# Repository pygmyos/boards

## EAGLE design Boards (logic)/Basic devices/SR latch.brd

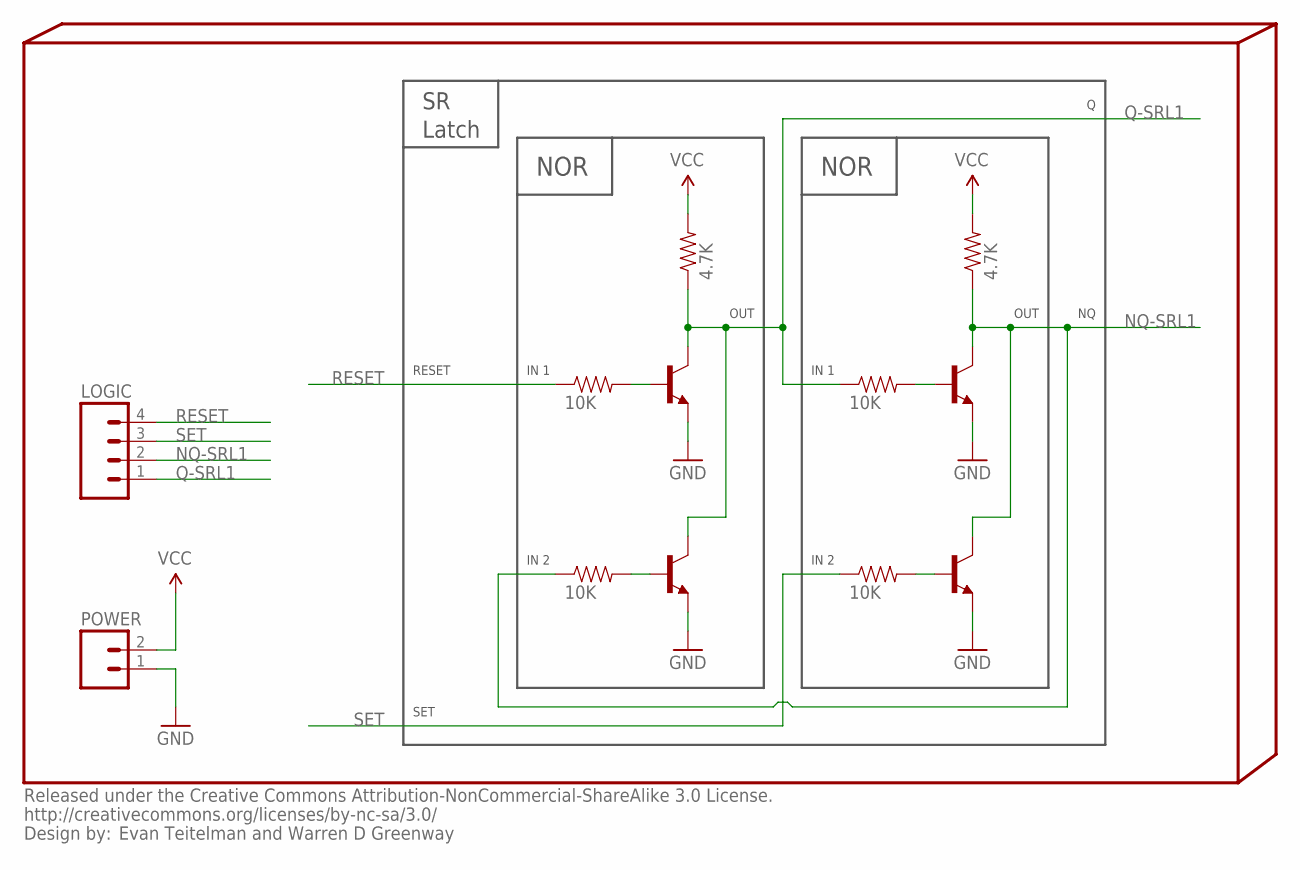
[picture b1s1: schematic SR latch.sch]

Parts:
INFO4: Evan Teitelman and Warren D Greenway; %CC-NC-SA
LOGIC: M04PTH; 1X04
POWER: M02PTH; 1X02
PUR-NOR1-SRL1, PUR-NOR2-SRL1: 4.7K; 0402-RES
Q1-NOR1-SRL1, Q1-NOR2-SRL1, Q2-NOR1-SRL1, Q2-NOR2-SRL1: TRANSISTOR_NPNSOT23; SOT23
R1-NOR1-SRL1, R1-NOR2-SRL1, R2-NOR1-SRL1, R2-NOR2-SRL1: 10K; 0402-RES

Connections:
GND: POWER.1, Q1-NOR1-SRL1.2 (E), Q1-NOR2-SRL1.2 (E), Q2-NOR1-SRL1.2 (E), Q2-NOR2-SRL1.2 (E)
unnamed: Q1-NOR2-SRL1.1 (B), R1-NOR2-SRL1.2
unnamed: Q2-NOR2-SRL1.1 (B), R2-NOR2-SRL1.2
unnamed: Q1-NOR1-SRL1.1 (B), R1-NOR1-SRL1.2
unnamed: Q2-NOR1-SRL1.1 (B), R2-NOR1-SRL1.2
NQ-SRL1: LOGIC.2, PUR-NOR1-SRL1.1, Q1-NOR1-SRL1.3 (C), Q2-NOR1-SRL1.3 (C), R2-NOR2-SRL1.1
Q-SRL1: LOGIC.1, PUR-NOR2-SRL1.1, Q1-NOR2-SRL1.3 (C), Q2-NOR2-SRL1.3 (C), R1-NOR1-SRL1.1
RESET: LOGIC.4, R1-NOR2-SRL1.1
SET: LOGIC.3, R2-NOR1-SRL1.1
VCC: POWER.2, PUR-NOR1-SRL1.2, PUR-NOR2-SRL1.2

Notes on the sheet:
NOR
IN 2
OUT
IN 1
SET
RESET
Latch

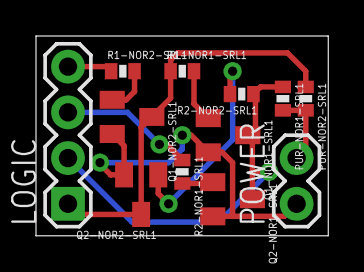
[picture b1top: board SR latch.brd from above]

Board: 2 copper layers, 16.2 x 11.1 mm, 13 parts (0 on the bottom side), 10 nets.

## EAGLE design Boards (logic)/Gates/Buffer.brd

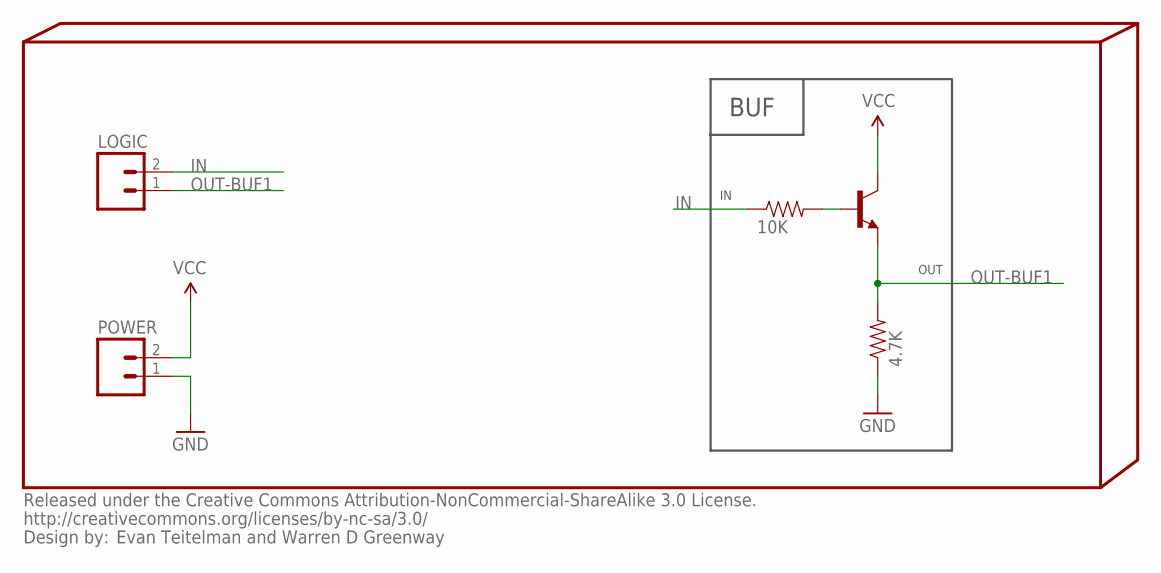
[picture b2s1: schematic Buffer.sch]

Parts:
INFO4: Evan Teitelman and Warren D Greenway; %CC-NC-SA
LOGIC: M02PTH; 1X02
PDR-BUF1: 4.7K; 0402-RES
POWER: M02PTH; 1X02
Q-BUF1: TRANSISTOR_NPNSOT23; SOT23
R-BUF1: 10K; 0402-RES

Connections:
GND: PDR-BUF1.1, POWER.1
IN: LOGIC.2, R-BUF1.1
unnamed: Q-BUF1.1 (B), R-BUF1.2
OUT-BUF1: LOGIC.1, PDR-BUF1.2, Q-BUF1.2 (E)
VCC: POWER.2, Q-BUF1.3 (C)

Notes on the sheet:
BUF
OUT

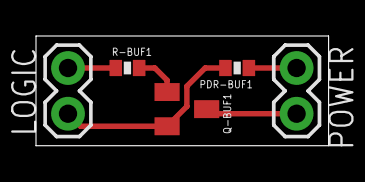
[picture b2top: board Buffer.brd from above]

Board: 2 copper layers, 16.3 x 6.1 mm, 6 parts (0 on the bottom side), 5 nets.

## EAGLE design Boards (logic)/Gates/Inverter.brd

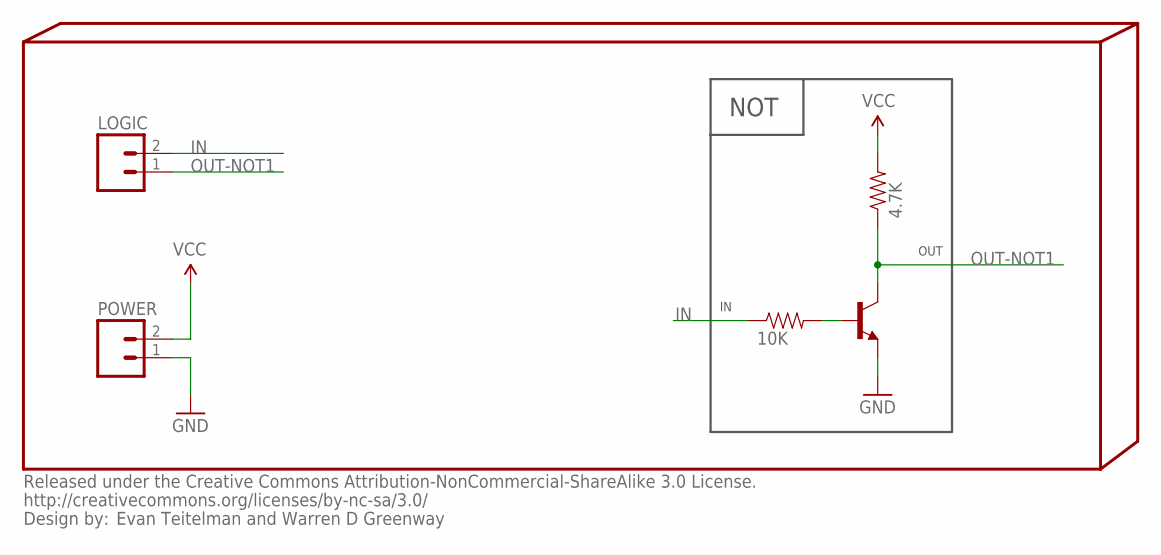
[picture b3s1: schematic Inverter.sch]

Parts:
INFO4: Evan Teitelman and Warren D Greenway; %CC-NC-SA
LOGIC: M02PTH; 1X02
POWER: M02PTH; 1X02
PUR-NOT1: 4.7K; 0402-RES
Q-NOT1: TRANSISTOR_NPNSOT23; SOT23
R-NOT1: 10K; 0402-RES

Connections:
GND: POWER.1, Q-NOT1.2 (E)
IN: LOGIC.2, R-NOT1.1
unnamed: Q-NOT1.1 (B), R-NOT1.2
OUT-NOT1: LOGIC.1, PUR-NOT1.1, Q-NOT1.3 (C)
VCC: POWER.2, PUR-NOT1.2

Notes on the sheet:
NOT
OUT

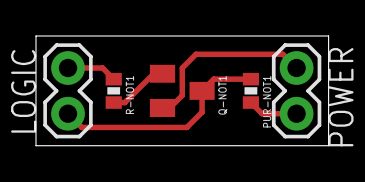
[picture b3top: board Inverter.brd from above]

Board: 2 copper layers, 16.3 x 6.1 mm, 6 parts (0 on the bottom side), 5 nets.

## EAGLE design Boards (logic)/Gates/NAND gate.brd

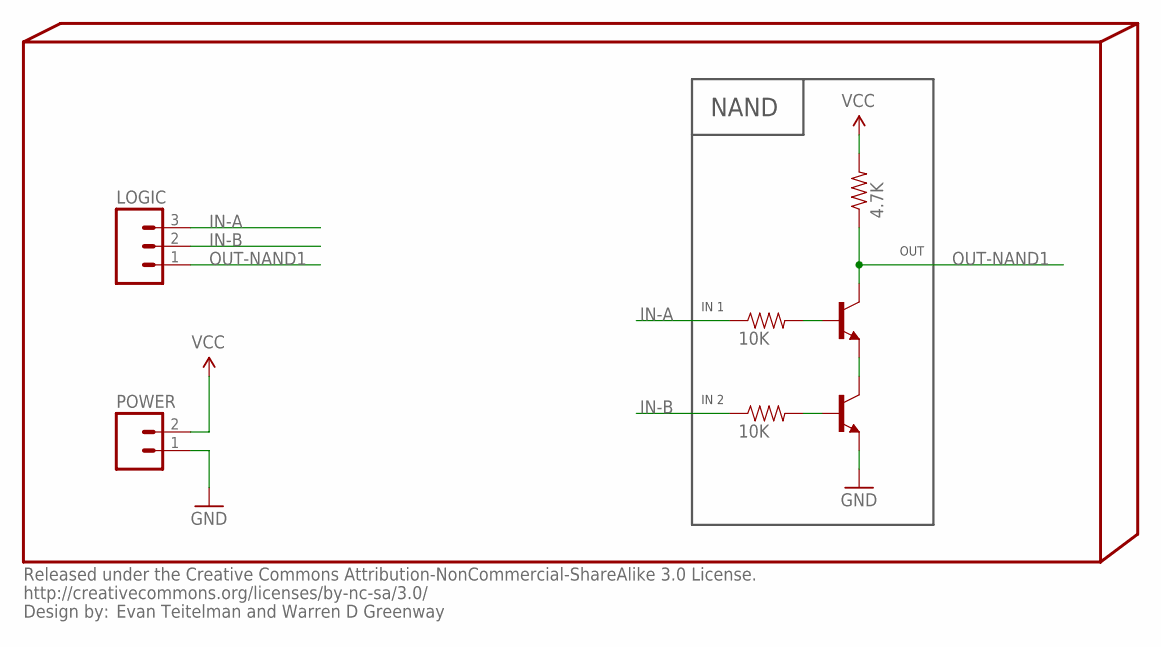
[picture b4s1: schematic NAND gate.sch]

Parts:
INFO4: Evan Teitelman and Warren D Greenway; %CC-NC-SA
LOGIC: M03PTH; 1X03
POWER: M02PTH; 1X02
PUR-NAND1: 4.7K; 0402-RES
Q1-NAND1, Q2-NAND1: TRANSISTOR_NPNSOT23; SOT23
R1-NAND1, R2-NAND2: 10K; 0402-RES

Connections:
GND: POWER.1, Q2-NAND1.2 (E)
IN-A: LOGIC.3, R1-NAND1.1
IN-B: LOGIC.2, R2-NAND2.1
unnamed: Q1-NAND1.1 (B), R1-NAND1.2
unnamed: Q2-NAND1.1 (B), R2-NAND2.2
OUT-NAND1: LOGIC.1, PUR-NAND1.1, Q1-NAND1.3 (C)
Q-Q-NAND1: Q1-NAND1.2 (E), Q2-NAND1.3 (C)
VCC: POWER.2, PUR-NAND1.2

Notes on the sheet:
NAND
IN 2
OUT
IN 1

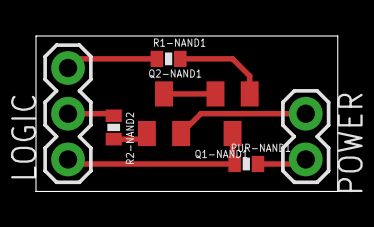
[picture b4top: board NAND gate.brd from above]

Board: 2 copper layers, 16.8 x 8.6 mm, 8 parts (0 on the bottom side), 8 nets.

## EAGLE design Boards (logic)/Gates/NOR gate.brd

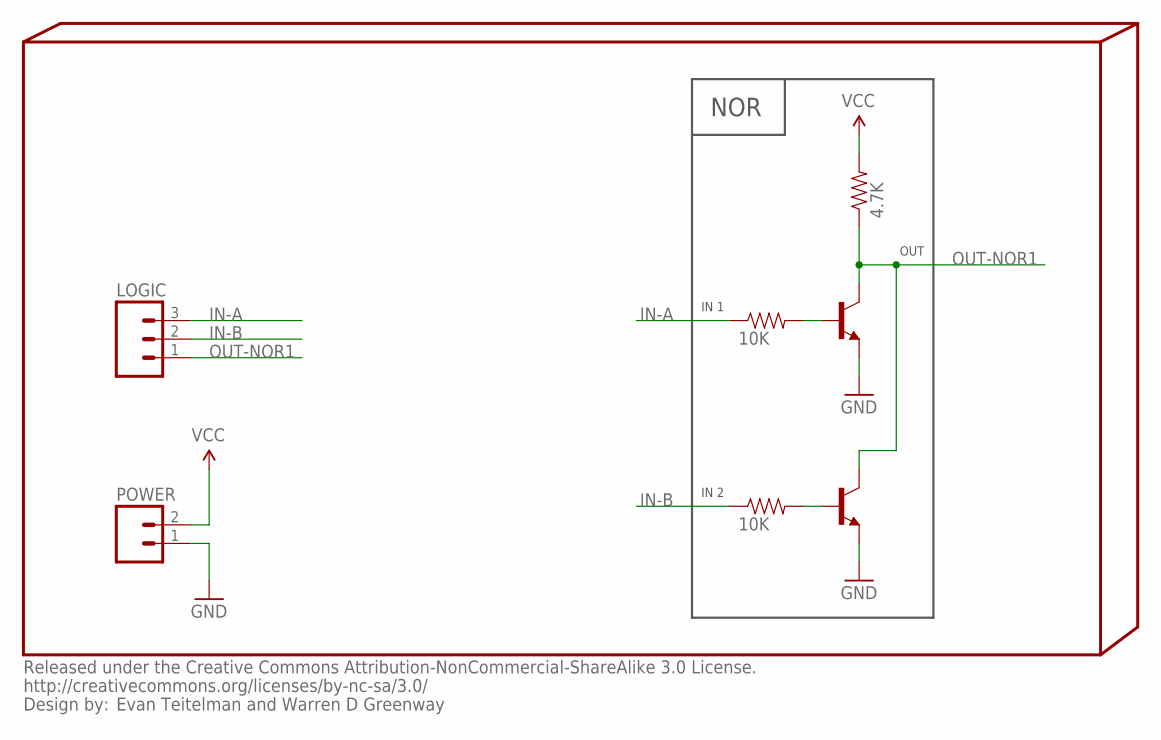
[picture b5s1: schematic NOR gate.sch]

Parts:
INFO4: Evan Teitelman and Warren D Greenway; %CC-NC-SA
LOGIC: M03PTH; 1X03
POWER: M02PTH; 1X02
PUR-NOR1: 4.7K; 0402-RES
Q1-NOR1, Q2-NOR1: TRANSISTOR_NPNSOT23; SOT23
R1-NOR1, R2-NOR1: 10K; 0402-RES

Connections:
GND: POWER.1, Q1-NOR1.2 (E), Q2-NOR1.2 (E)
IN-A: LOGIC.3, R1-NOR1.1
IN-B: LOGIC.2, R2-NOR1.1
unnamed: Q1-NOR1.1 (B), R1-NOR1.2
unnamed: Q2-NOR1.1 (B), R2-NOR1.2
OUT-NOR1: LOGIC.1, PUR-NOR1.1, Q1-NOR1.3 (C), Q2-NOR1.3 (C)
VCC: POWER.2, PUR-NOR1.2

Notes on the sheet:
NOR
IN 2
OUT
IN 1

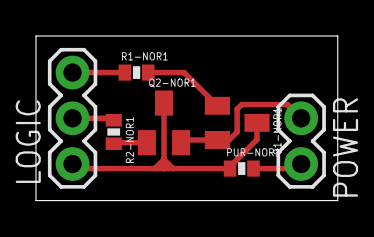
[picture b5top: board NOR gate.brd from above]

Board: 2 copper layers, 16.8 x 9.1 mm, 8 parts (0 on the bottom side), 7 nets.

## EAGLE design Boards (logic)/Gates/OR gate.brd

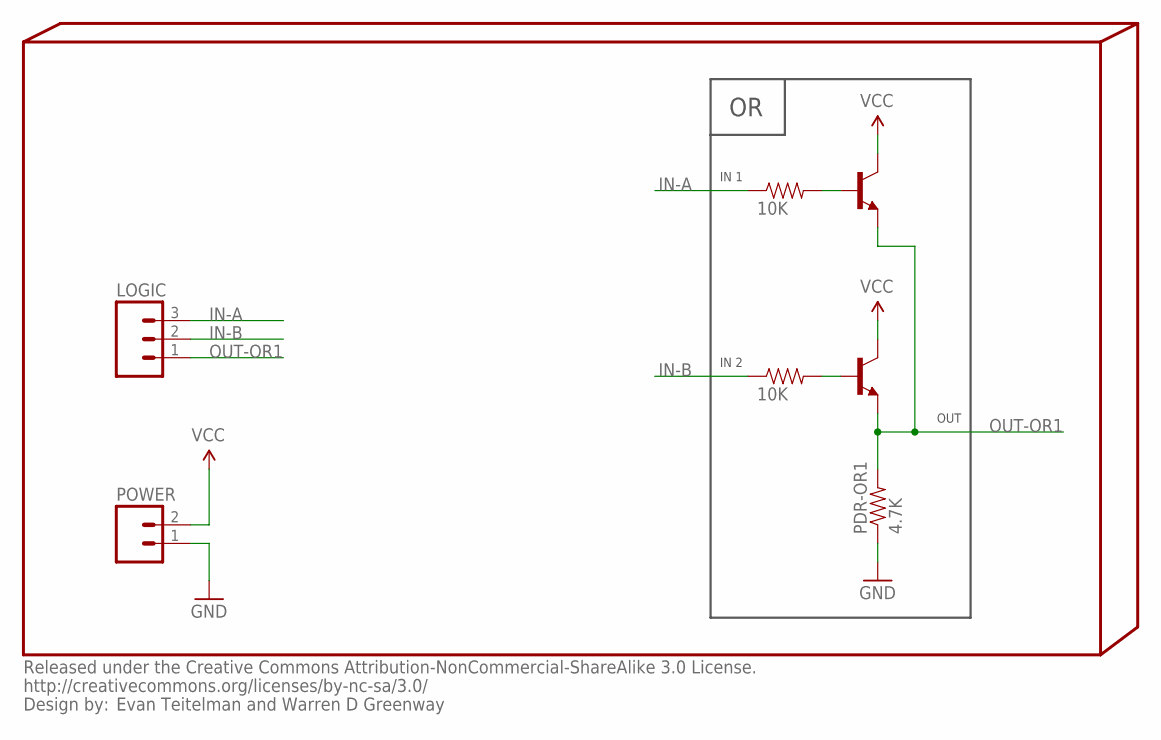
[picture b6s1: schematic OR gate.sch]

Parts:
INFO4: Evan Teitelman and Warren D Greenway; %CC-NC-SA
LOGIC: M03PTH; 1X03
PDR-OR1: 4.7K; 0402-RES
POWER: M02PTH; 1X02
Q1-OR1, Q2-OR1: TRANSISTOR_NPNSOT23; SOT23
R1-OR1, R2-OR1: 10K; 0402-RES

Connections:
GND: PDR-OR1.1, POWER.1
IN-A: LOGIC.3, R1-OR1.1
IN-B: LOGIC.2, R2-OR1.1
unnamed: Q1-OR1.1 (B), R1-OR1.2
unnamed: Q2-OR1.1 (B), R2-OR1.2
OUT-OR1: LOGIC.1, PDR-OR1.2, Q1-OR1.2 (E), Q2-OR1.2 (E)
VCC: POWER.2, Q1-OR1.3 (C), Q2-OR1.3 (C)

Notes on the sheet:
IN 2
OUT
IN 1

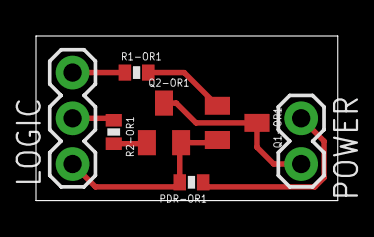
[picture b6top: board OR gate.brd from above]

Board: 2 copper layers, 16.8 x 9.1 mm, 8 parts (0 on the bottom side), 7 nets.
